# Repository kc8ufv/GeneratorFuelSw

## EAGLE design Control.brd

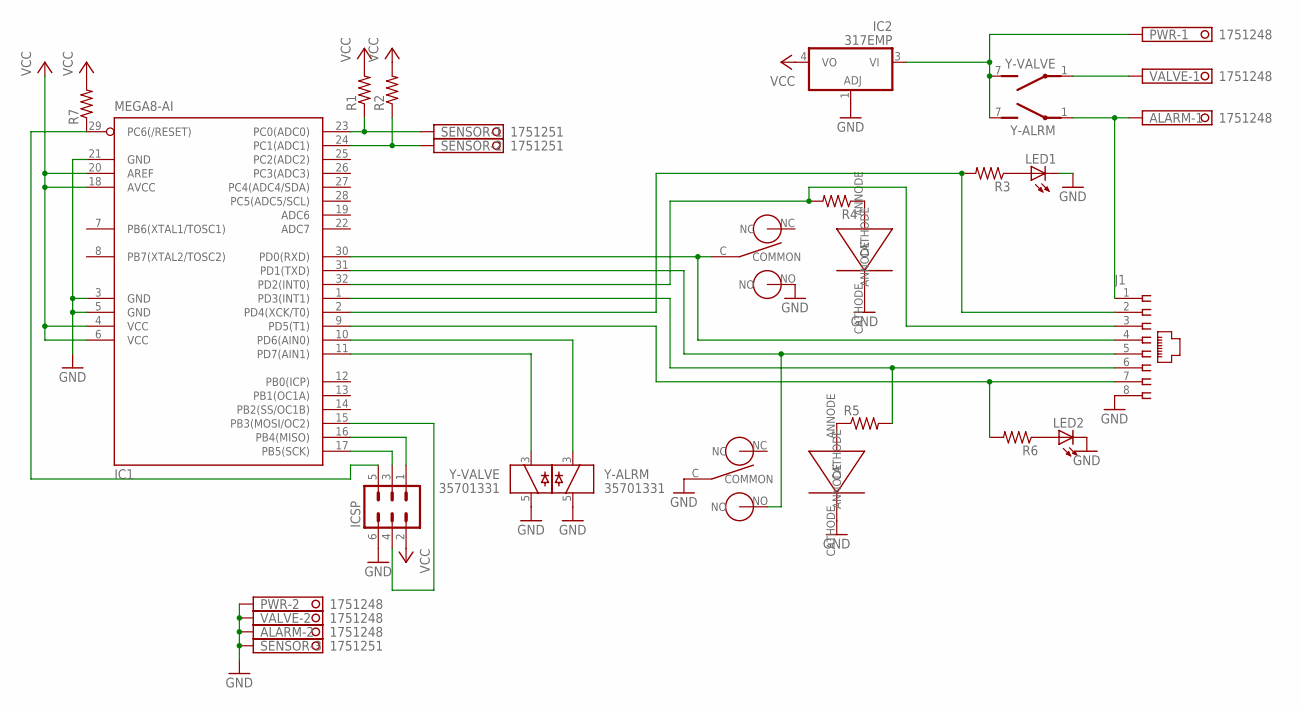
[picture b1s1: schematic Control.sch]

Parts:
ALARM: 1751248
BUTTON1, BUTTON2: LED-BUTTON-16MM; 16MM
IC1: MEGA8-AI; TQFP32-08
IC2: 317EMP; SOT223
ICSP: MA03-2
J1: 215877-7
LED1, LED2: LED5MM
PWR: 1751248
R1, R2, R3, R4, R5, R6, R7: R-US_M0805; M0805
SENSOR: 1751251
VALVE: 1751248
Y-ALRM: 35701331; REED
Y-VALVE: 35701331; REED

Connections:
GND: ALARM.2, BUTTON1.CATHODE, BUTTON1.NO, BUTTON2.C (COMMON), BUTTON2.CATHODE, IC1.3 (GND), IC1.5 (GND), IC1.21 (GND), IC2.1 (ADJ), ICSP.6, J1.8, LED1.K (C), LED2.K (C), PWR.2, SENSOR.3, VALVE.2, Y-ALRM.5, Y-VALVE.5
unnamed: ALARM.1, J1.1, Y-ALRM.1
unnamed: VALVE.1, Y-VALVE.1
unnamed: IC1.23 (PC0(ADC0)), R1.1, SENSOR.1
unnamed: IC1.24 (PC1(ADC1)), R2.1, SENSOR.2
unnamed: IC1.32 (PD2(INT0)), J1.3, R4.2
unnamed: IC1.1 (PD3(INT1)), J1.6, R5.2
unnamed: LED1.A, R3.1
unnamed: BUTTON2.ANNODE, R5.1
unnamed: LED2.A, R6.1
unnamed: BUTTON1.ANNODE, R4.1
unnamed: BUTTON1.C (COMMON), IC1.30 (PD0(RXD)), J1.4
unnamed: BUTTON2.NO, IC1.31 (PD1(TXD)), J1.5
unnamed: IC1.2 (PD4(XCK/T0)), J1.2, R3.2
unnamed: IC1.9 (PD5(T1)), J1.7, R6.2
unnamed: IC1.11 (PD7(AIN1)), Y-VALVE.3
unnamed: IC1.10 (PD6(AIN0)), Y-ALRM.3
unnamed: IC1.29 (PC6(/RESET)), ICSP.5, R7.1
unnamed: IC1.16 (PB4(MISO)), ICSP.1
unnamed: IC1.17 (PB5(SCK)), ICSP.3
unnamed: IC1.15 (PB3(MOSI/OC2)), ICSP.4
VCC: IC1.4 (VCC), IC1.6 (VCC), IC1.18 (AVCC), IC1.20 (AREF), IC2.4 (VO), ICSP.2, R1.2, R2.2, R7.2
VIN: IC2.3 (VI), PWR.1, Y-ALRM.7 (S), Y-VALVE.7 (S)

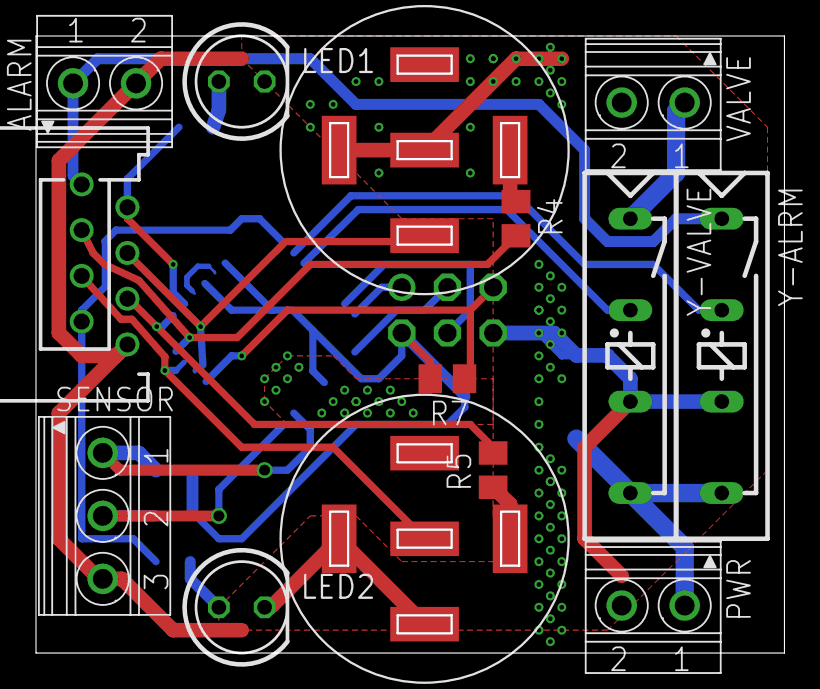
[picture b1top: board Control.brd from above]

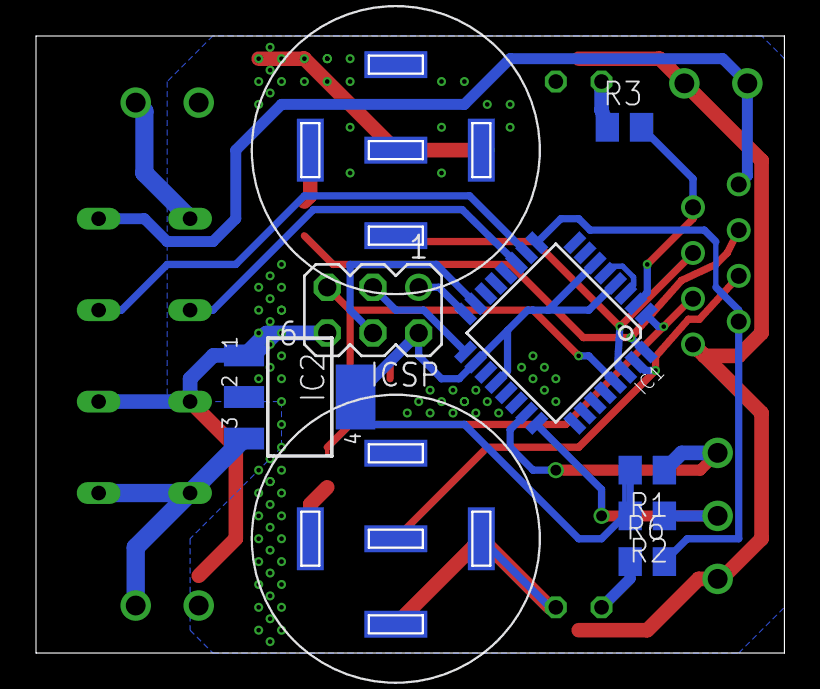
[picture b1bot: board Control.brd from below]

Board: 2 copper layers, 41.5 x 34.2 mm, 21 parts (7 on the bottom side), 23 nets.

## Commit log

2020-01-25 Initial upload of generator fuel switch
